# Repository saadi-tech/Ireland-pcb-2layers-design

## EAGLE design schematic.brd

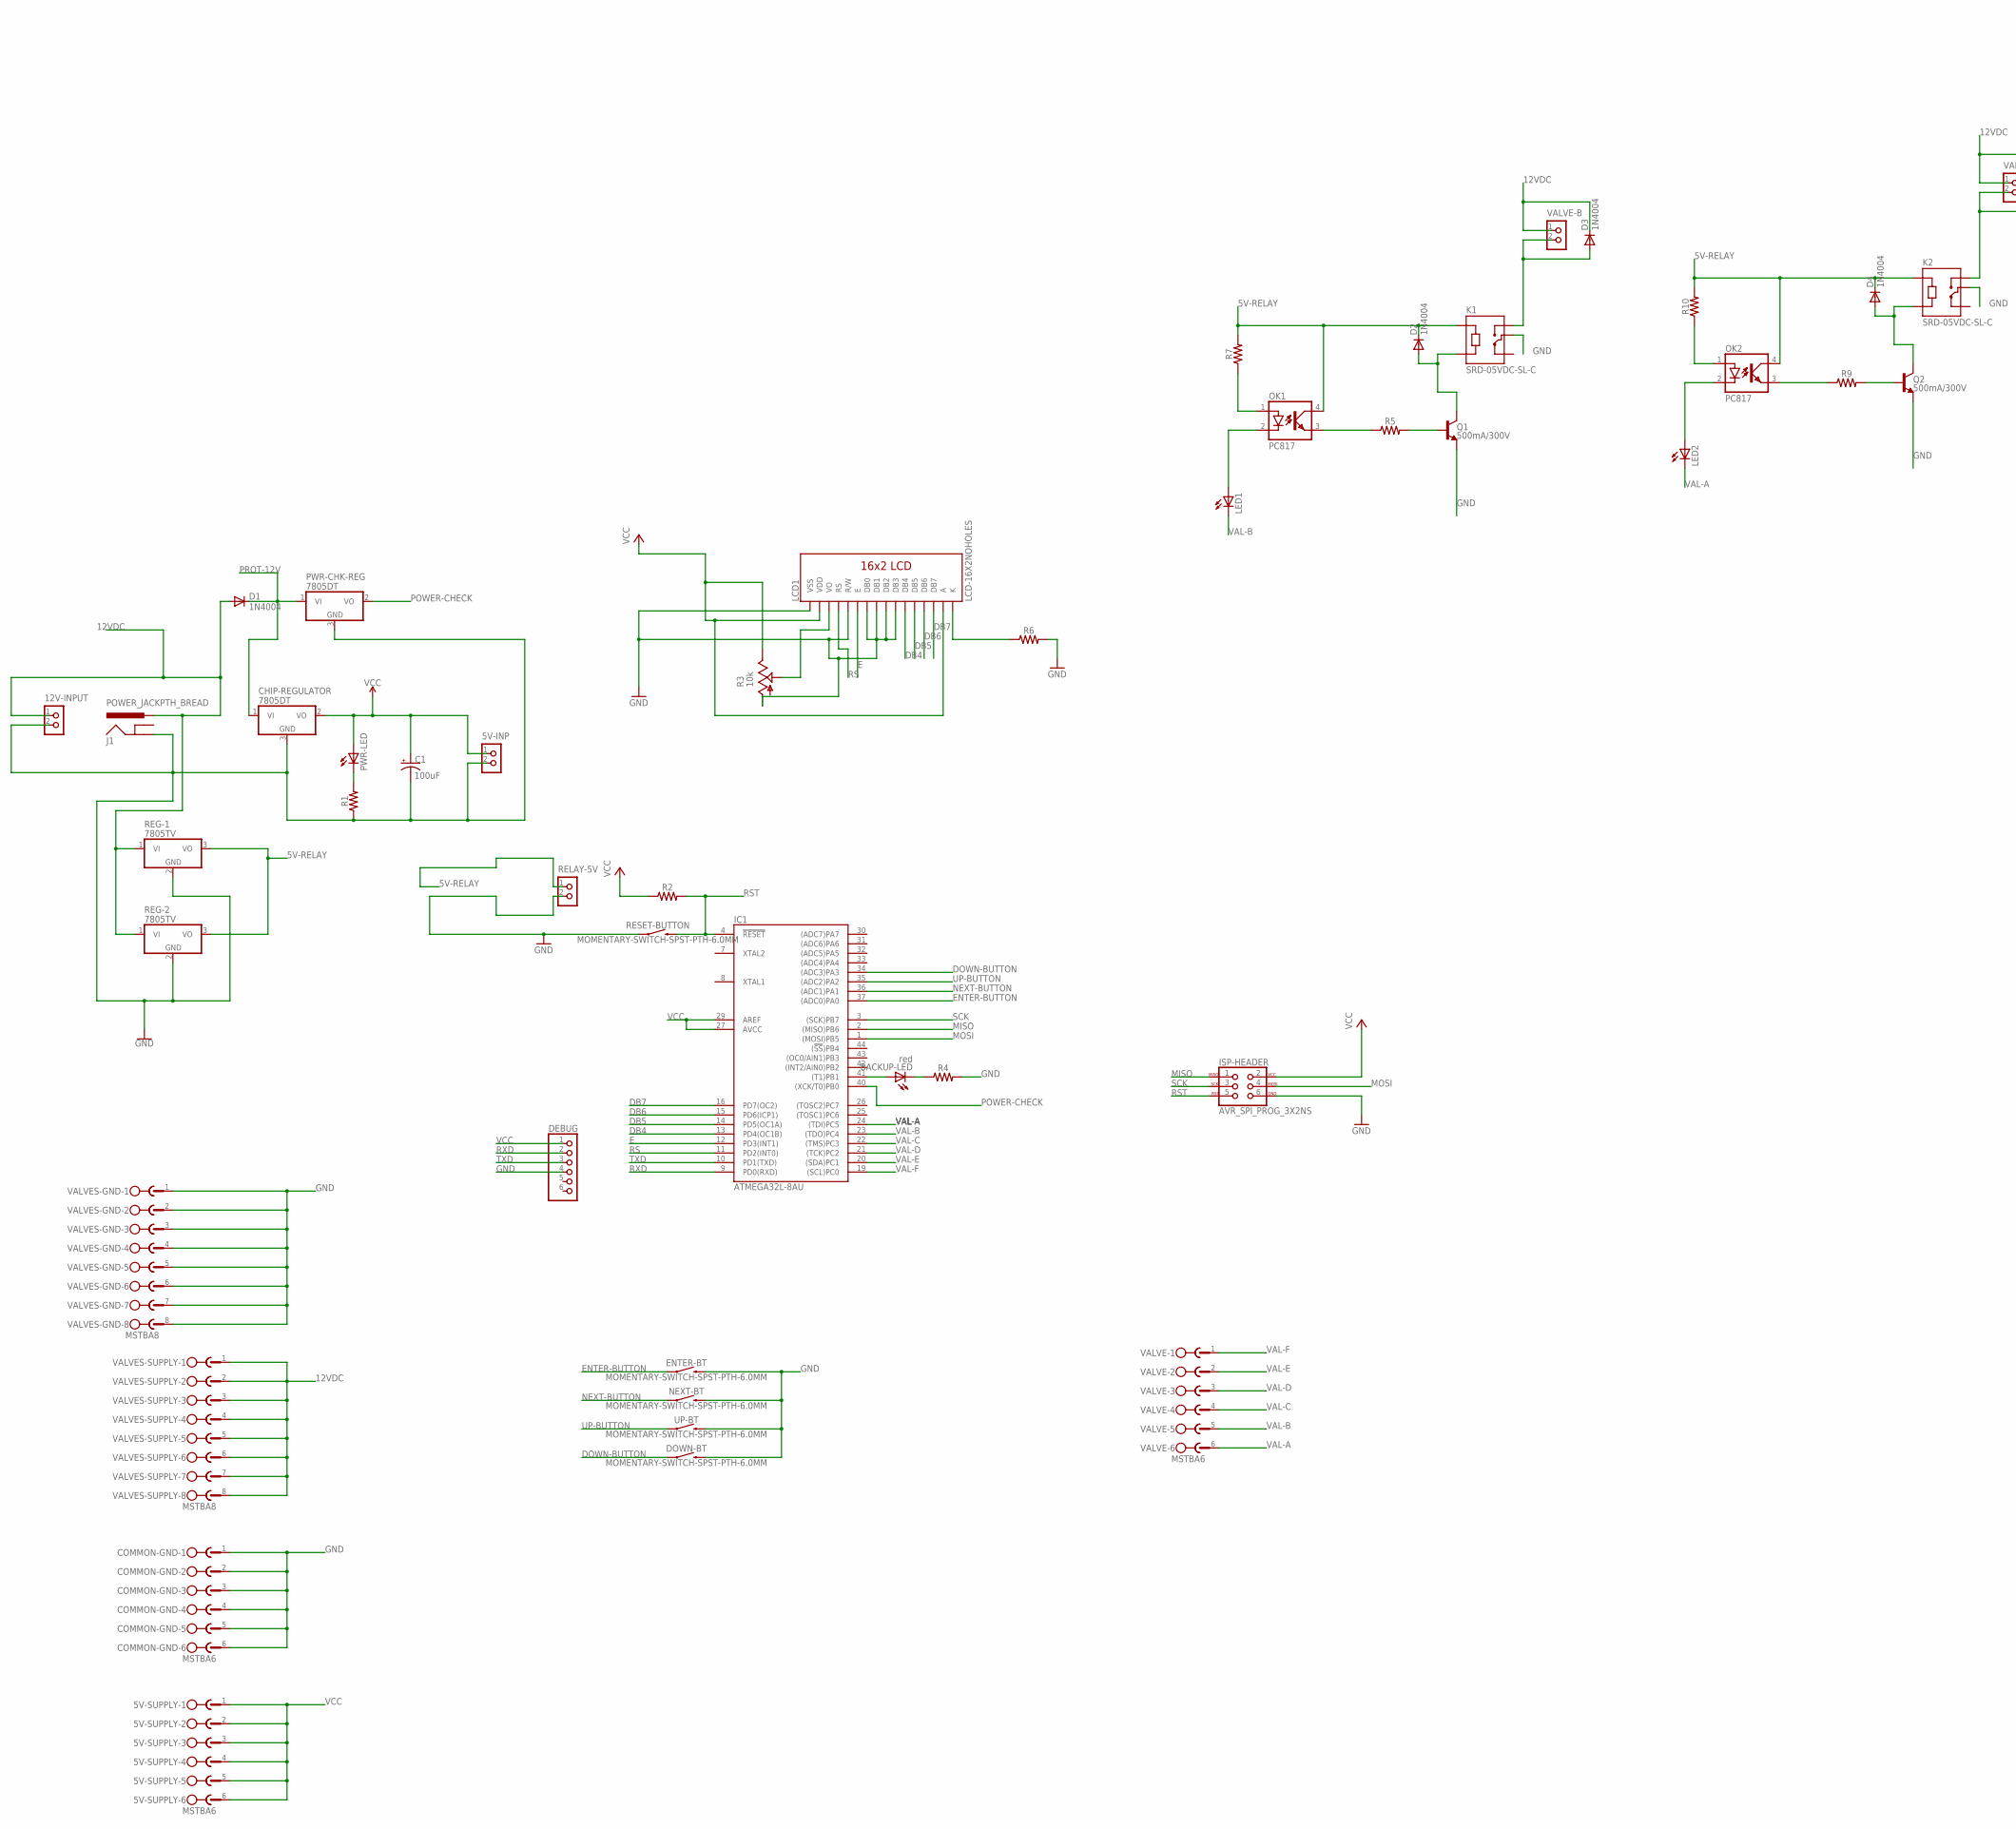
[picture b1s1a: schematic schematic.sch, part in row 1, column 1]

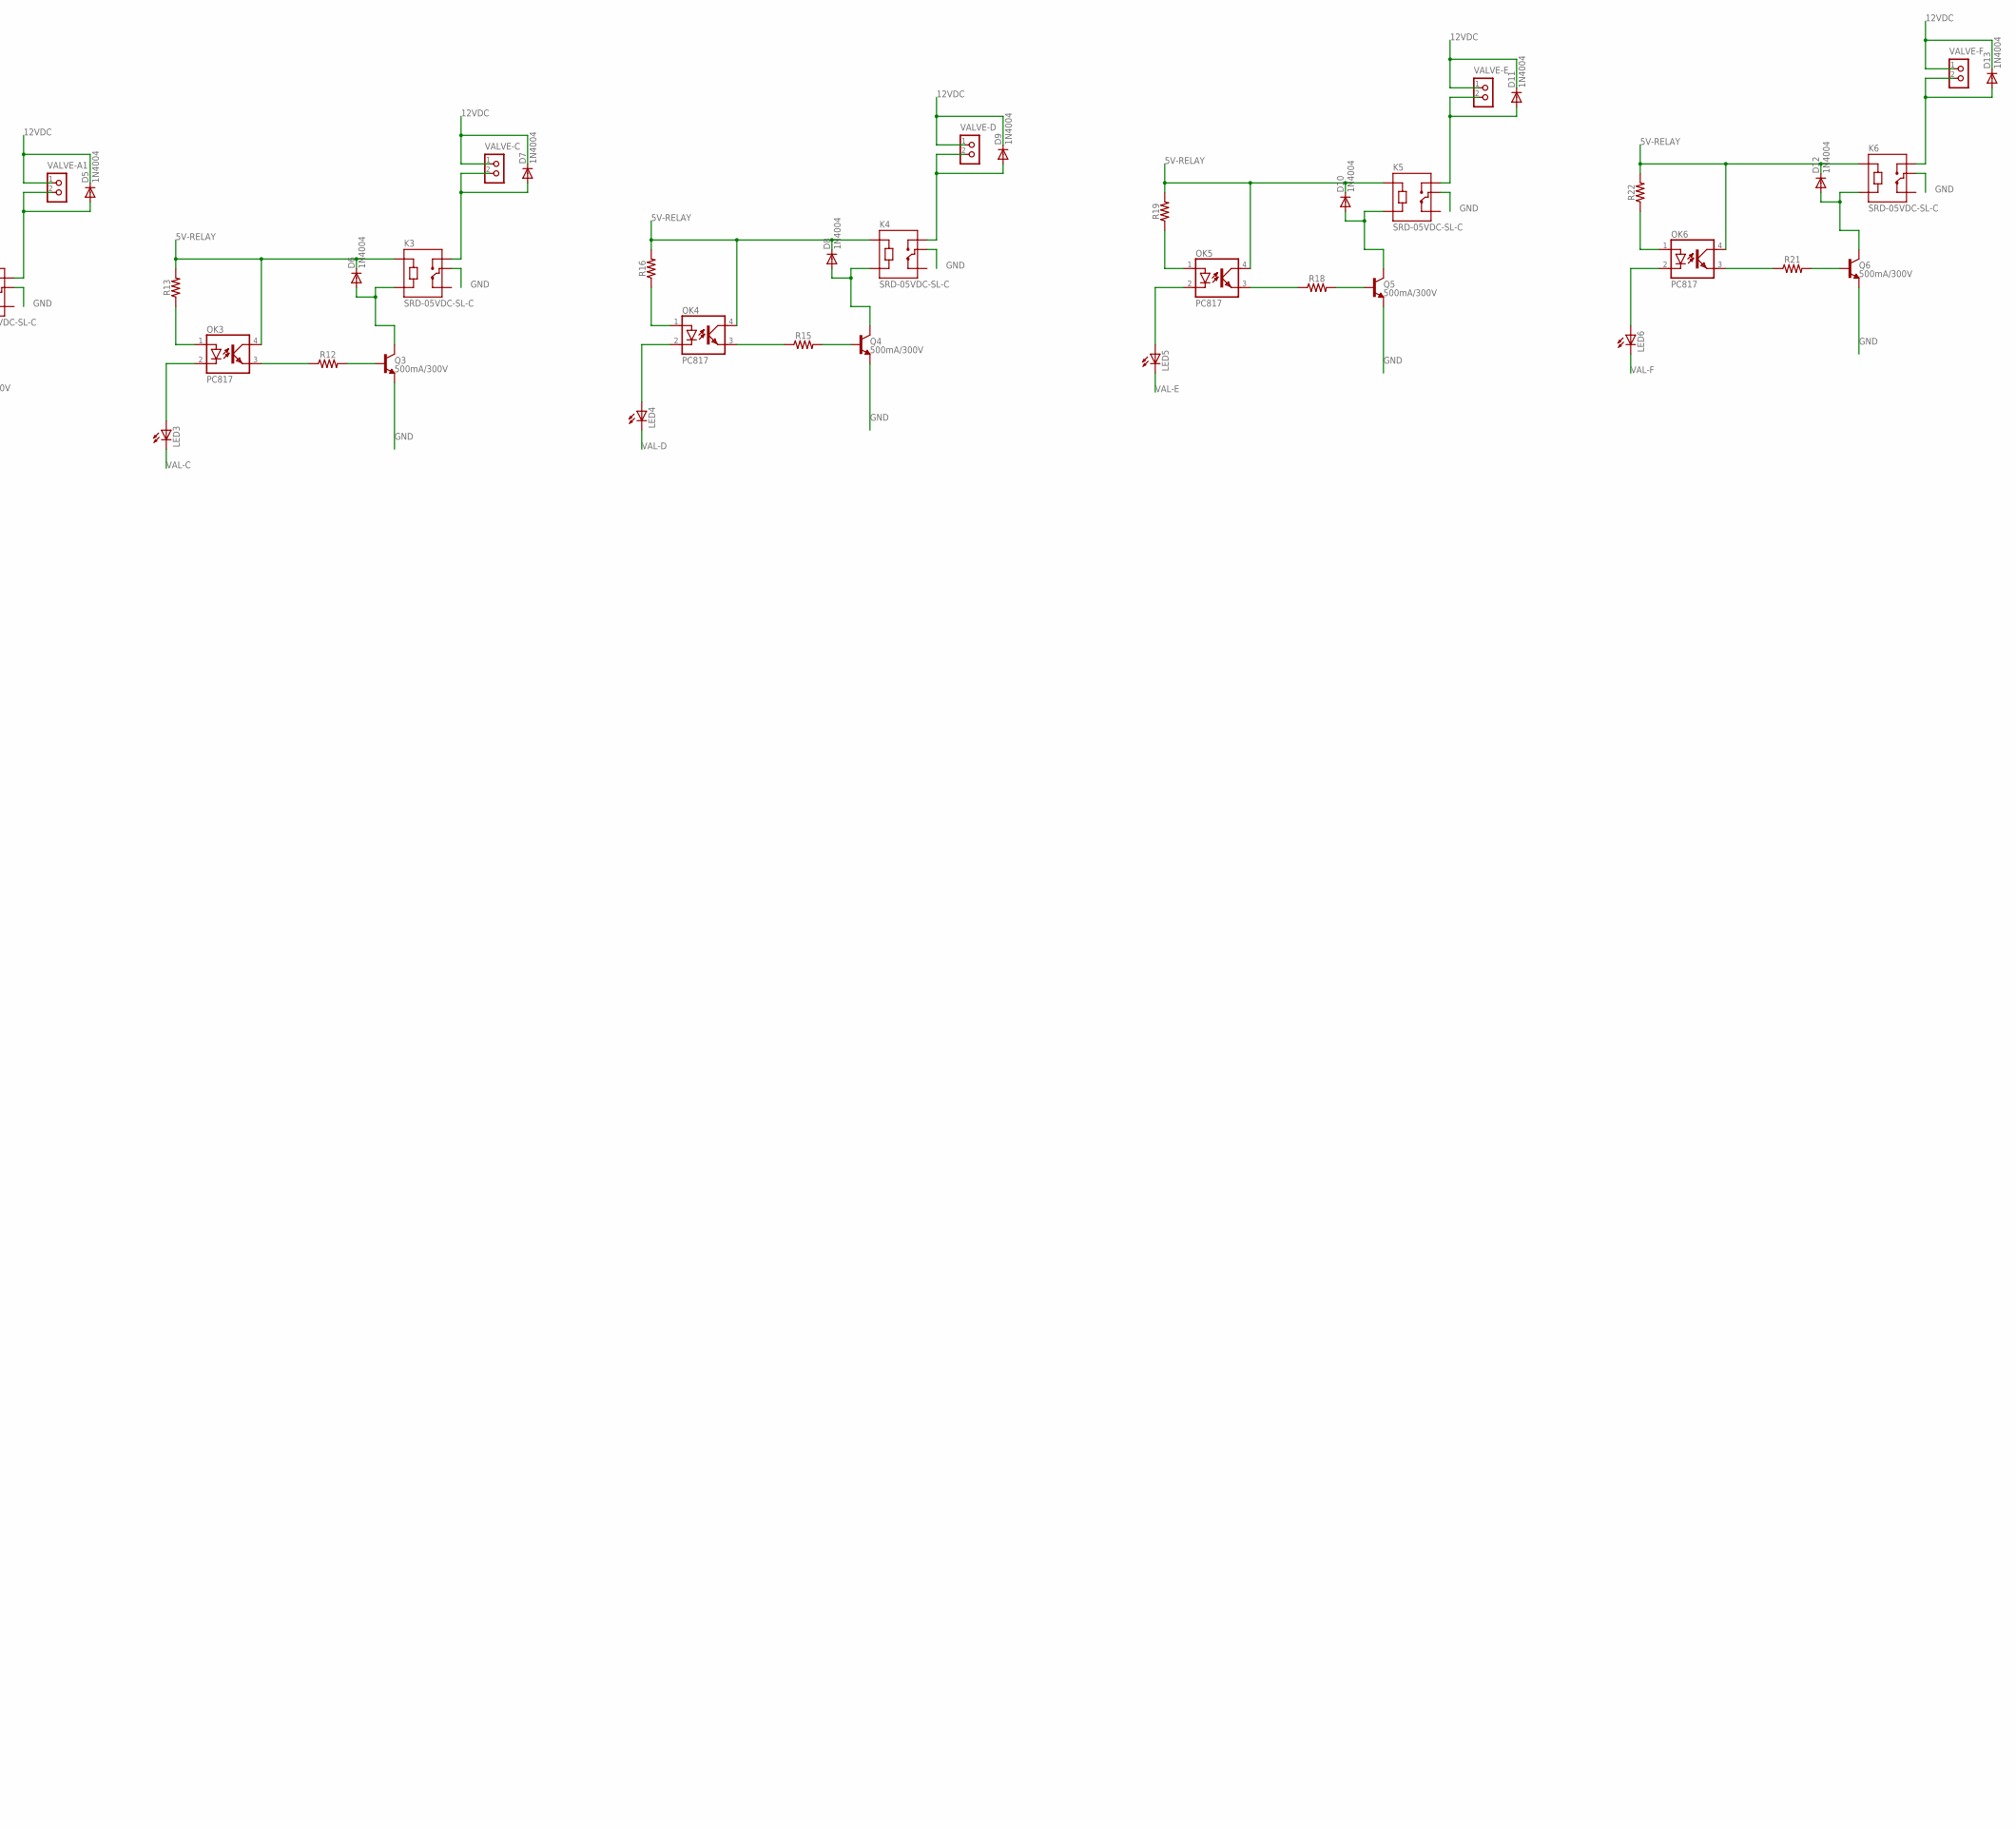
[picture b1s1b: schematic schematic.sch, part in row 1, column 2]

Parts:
5V-INP, 12V-INPUT: CON_TERMINAL_BLOCK_02-5MM; TERMINAL_BLOCK_2P_5
5V-SUPPLY: MSTBA6
BACKUP-LED: red; LED-1206
C1: 100uF; CPOL-RADIAL-2.5MM-6.5MM
CHIP-REGULATOR: 7805DT; TO252
COMMON-GND: MSTBA6
D1, D2, D3, D4, D5, D6, D7, D8, D9, D10, D11, D12, D13: 1N4004; DO41-10
DEBUG: PINHD-1X6B; 1X06-BIG
DOWN-BT: MOMENTARY-SWITCH-SPST-PTH-6.0MM; TACTILE_SWITCH_PTH_6.0MM
ENTER-BT: MOMENTARY-SWITCH-SPST-PTH-6.0MM; TACTILE_SWITCH_PTH_6.0MM
IC1: ATMEGA32L-8AU; QFP44_10X10_0.80
ISP-HEADER: AVR_SPI_PROG_3X2NS; 2X3-NS
J1: POWER_JACKPTH_BREAD; POWER_JACK_PTH_BREAD
K1, K2, K3, K4, K5, K6: SRD-05VDC-SL-C; RELAY_SRD-05VDC-SL-C
LCD1: LCD-16X2NOHOLES; LCD-16X2_NOHOLESNOSILK
LED1, LED2, LED3, LED4, LED5, LED6: LED1206; LED-1206
NEXT-BT: MOMENTARY-SWITCH-SPST-PTH-6.0MM; TACTILE_SWITCH_PTH_6.0MM
OK1, OK2, OK3, OK4, OK5, OK6: PC817; DIL04
PWR-CHK-REG: 7805DT; TO252
PWR-LED: LED1206; LED-1206
Q1, Q2, Q3, Q4, Q5, Q6: 500mA/300V; SOT23-3
R1, R2, R4, R5, R6, R7, R9, R10, R12, R13, R15, R16, R18, R19, R21, R22: 1206
R3: 10k; CA6V
REG-1, REG-2: 7805TV; TO220V
RELAY-5V: CON_TERMINAL_BLOCK_02-5MM; TERMINAL_BLOCK_2P_5
RESET-BUTTON: MOMENTARY-SWITCH-SPST-PTH-6.0MM; TACTILE_SWITCH_PTH_6.0MM
UP-BT: MOMENTARY-SWITCH-SPST-PTH-6.0MM; TACTILE_SWITCH_PTH_6.0MM
VALVE: MSTBA6
VALVE-A1: CON_TERMINAL_BLOCK_02-5MM; TERMINAL_BLOCK_2P_5
VALVE-B: CON_TERMINAL_BLOCK_02-5MM; TERMINAL_BLOCK_2P_5
VALVE-C: CON_TERMINAL_BLOCK_02-5MM; TERMINAL_BLOCK_2P_5
VALVE-D: CON_TERMINAL_BLOCK_02-5MM; TERMINAL_BLOCK_2P_5
VALVE-E: CON_TERMINAL_BLOCK_02-5MM; TERMINAL_BLOCK_2P_5
VALVE-F: CON_TERMINAL_BLOCK_02-5MM; TERMINAL_BLOCK_2P_5
VALVES-GND: MSTBA8
VALVES-SUPPLY: MSTBA8

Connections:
5V-RELAY: D2.C, D4.C, D6.C, D8.C, D10.C, D12.C, K1.A1, K2.A1, K3.A1, K4.A1, K5.A1, K6.A1, OK1.4 (COL), OK2.4 (COL), OK3.4 (COL), OK4.4 (COL), OK5.4 (COL), OK6.4 (COL), R7.2, R10.2, R13.2, R16.2, R19.2, R22.2, REG-1.3 (VO), REG-2.3 (VO), RELAY-5V.1
12VDC: 12V-INPUT.1, D1.A, D3.C, D5.C, D7.C, D9.C, D11.C, D13.C, J1.PWR, REG-1.1 (VI), REG-2.1 (VI), VALVE-A1.1, VALVE-B.1, VALVE-C.1, VALVE-D.1, VALVE-E.1, VALVE-F.1, VALVES-SUPPLY.1, VALVES-SUPPLY.2, VALVES-SUPPLY.3, VALVES-SUPPLY.4, VALVES-SUPPLY.5, VALVES-SUPPLY.6, VALVES-SUPPLY.7, VALVES-SUPPLY.8
DB4: IC1.13 (PD4(OC1B)), LCD1.11 (DB4)
DB5: IC1.14 (PD5(OC1A)), LCD1.12 (DB5)
DB6: IC1.15 (PD6(ICP1)), LCD1.13 (DB6)
DB7: IC1.16 (PD7(OC2)), LCD1.14 (DB7)
DOWN-BUTTON: DOWN-BT.1, IC1.34 ((ADC3)PA3)
E: IC1.12 (PD3(INT1)), LCD1.6 (E)
ENTER-BUTTON: ENTER-BT.1, IC1.37 ((ADC0)PA0)
GND: 5V-INP.2, 12V-INPUT.2, C1.2 (-), CHIP-REGULATOR.3 (GND), COMMON-GND.1, COMMON-GND.2, COMMON-GND.3, COMMON-GND.4, COMMON-GND.5, COMMON-GND.6, DEBUG.4, DOWN-BT.3 (2), ENTER-BT.3 (2), IC1.6 (GND), IC1.18 (GND), IC1.28 (GND), IC1.39 (GND), ISP-HEADER.6, J1.GND, K1.COM, K2.COM, K3.COM, K4.COM, K5.COM, K6.COM, LCD1.1 (VSS), LCD1.5 (R/W), LCD1.7 (DB0), LCD1.8 (DB1), LCD1.9 (DB2), LCD1.10 (DB3), NEXT-BT.3 (2), PWR-CHK-REG.3 (GND), Q1.2 (E), Q2.2 (E), Q3.2 (E), Q4.2 (E), Q5.2 (E), Q6.2 (E), R1.1, R3.A, R4.2, R6.2, REG-1.2 (GND), REG-2.2 (GND), RELAY-5V.2, RESET-BUTTON.1, UP-BT.3 (2), VALVES-GND.1, VALVES-GND.2, VALVES-GND.3, VALVES-GND.4, VALVES-GND.5, VALVES-GND.6, VALVES-GND.7, VALVES-GND.8
MISO: IC1.2 ((MISO)PB6), ISP-HEADER.1
MOSI: IC1.1 ((MOSI)PB5), ISP-HEADER.4
unnamed: LCD1.16 (K), R6.1
unnamed: PWR-LED.C, R1.2
unnamed: OK1.1 (A), R7.1
unnamed: BACKUP-LED.A, IC1.41 ((T1)PB1)
unnamed: BACKUP-LED.C, R4.1
unnamed: LCD1.3 (VO), R3.S
unnamed: LED1.A, OK1.2 (C)
unnamed: OK1.3 (EMIT), R5.1
unnamed: D2.A, K1.A2, Q1.3 (C)
unnamed: Q1.1 (B), R5.2
unnamed: OK2.1 (A), R10.1
unnamed: D3.A, K1.NO, VALVE-B.2
unnamed: LED2.A, OK2.2 (C)
unnamed: OK2.3 (EMIT), R9.1
unnamed: Q2.1 (B), R9.2
unnamed: D4.A, K2.A2, Q2.3 (C)
unnamed: D5.A, K2.NO, VALVE-A1.2
unnamed: OK3.1 (A), R13.1
unnamed: LED3.A, OK3.2 (C)
unnamed: OK3.3 (EMIT), R12.1
unnamed: Q3.1 (B), R12.2
unnamed: D6.A, K3.A2, Q3.3 (C)
unnamed: D7.A, K3.NO, VALVE-C.2
unnamed: OK4.1 (A), R16.1
unnamed: LED4.A, OK4.2 (C)
unnamed: OK4.3 (EMIT), R15.1
unnamed: Q4.1 (B), R15.2
unnamed: D8.A, K4.A2, Q4.3 (C)
unnamed: D9.A, K4.NO, VALVE-D.2
unnamed: OK5.1 (A), R19.1
unnamed: LED5.A, OK5.2 (C)
unnamed: OK5.3 (EMIT), R18.1
unnamed: Q5.1 (B), R18.2
unnamed: D10.A, K5.A2, Q5.3 (C)
unnamed: D11.A, K5.NO, VALVE-E.2
unnamed: OK6.1 (A), R22.1
unnamed: LED6.A, OK6.2 (C)
unnamed: OK6.3 (EMIT), R21.1
unnamed: Q6.1 (B), R21.2
unnamed: D12.A, K6.A2, Q6.3 (C)
unnamed: D13.A, K6.NO, VALVE-F.2
NEXT-BUTTON: IC1.36 ((ADC1)PA1), NEXT-BT.1
POWER-CHECK: IC1.40 ((XCK/T0)PB0), PWR-CHK-REG.2 (VO)
PROT-12V: CHIP-REGULATOR.1 (VI), D1.C, PWR-CHK-REG.1 (VI)
RS: IC1.11 (PD2(INT0)), LCD1.4 (RS)
RST: IC1.4 (!RESET), ISP-HEADER.5, R2.2, RESET-BUTTON.3 (2)
RXD: DEBUG.2, IC1.9 (PD0(RXD))
SCK: IC1.3 ((SCK)PB7), ISP-HEADER.3
TXD: DEBUG.3, IC1.10 (PD1(TXD))
UP-BUTTON: IC1.35 ((ADC2)PA2), UP-BT.1
VAL-A: IC1.24 ((TDI)PC5), LED2.C, VALVE.6
VAL-B: IC1.23 ((TDO)PC4), LED1.C, VALVE.5
VAL-C: IC1.22 ((TMS)PC3), LED3.C, VALVE.4
VAL-D: IC1.21 ((TCK)PC2), LED4.C, VALVE.3
VAL-E: IC1.20 ((SDA)PC1), LED5.C, VALVE.2
VAL-F: IC1.19 ((SCL)PC0), LED6.C, VALVE.1
VCC: 5V-INP.1, 5V-SUPPLY.1, 5V-SUPPLY.2, 5V-SUPPLY.3, 5V-SUPPLY.4, 5V-SUPPLY.5, 5V-SUPPLY.6, C1.1 (+), CHIP-REGULATOR.2 (VO), DEBUG.1, IC1.5 (VCC), IC1.17 (VCC), IC1.27 (AVCC), IC1.29 (AREF), IC1.38 (VCC), ISP-HEADER.2, LCD1.2 (VDD), LCD1.15 (A), PWR-LED.A, R2.1, R3.E

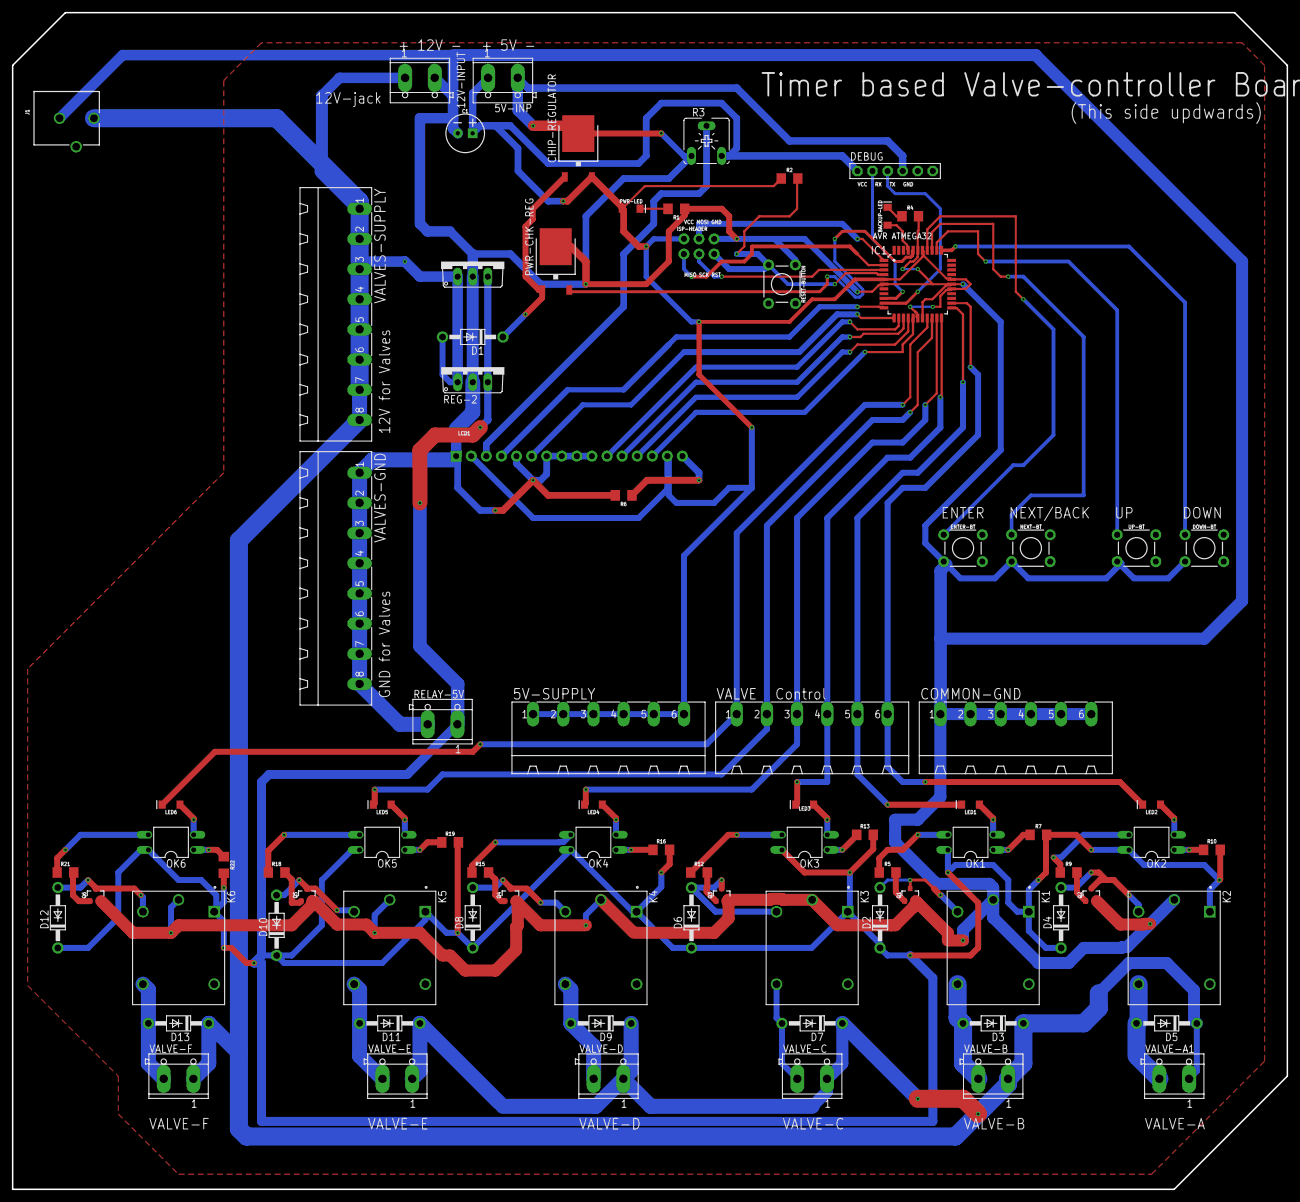
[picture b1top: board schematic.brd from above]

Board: 2 copper layers, 214.6 x 198.1 mm, 85 parts (0 on the bottom side), 69 nets.

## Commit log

2020-10-24 design of PCB is reade...
2020-10-24 Please enter the commit message for your changes. Lines starting
2020-10-29 test commit by me
2020-10-31 test commit

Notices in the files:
parts and their libraries:
SparkFun-Retired: Licensing: Creative Commons ShareAlike 4.0 International - https://creativecommons.org/licenses/by-sa/4.0
